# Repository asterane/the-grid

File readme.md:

# The Grid

# Table of Contents

1.  [Under Construction](#org4e31319)
2.  [Overview](#orgddce423)
3.  [Project Goals](#org27a8e06)
    1.  [Overall](#orgf33c17d)
    2.  [Design](#org3ddfc4e)
    3.  [Implementation](#orge4cc2e5)
4.  [System](#orgab08084)
    1.  [Origins](#org15afbf3)
    2.  [Considerations](#org984049b)
    3.  [Examination](#org4223284)
        1.  [Board](#org9094cac)
        2.  [Cube](#org7cbf77a)
        3.  [Column](#org4744b31)
        4.  [Grid](#orgfe13412)
        5.  [Control](#org2ae035e)
5.  [Structure](#org9b584a7)
6.  [Electronics](#orgca242fe)
7.  [Software](#org8aeed29)
8.  [Reflection](#org893cef3)

# Under Construction

This readme file will become much more extensive in the future.

# Overview

By far my most challenging and ambitious engineering project up to its
time, the Grid was a massive lighted display board which served as a
set piece for the play in my senior year of high school. The image
above shows the first time the entire Grid lit up at once. This
display wall was composed of 60 wooden cubes, each two feet by two
feet, for a total size of twenty feet at the base by twelve feet in
height. Every cube contained four high power red-green-blue (RGB)
light emitting diodes (LED) and acted as a single pixel.

A complex system, the Grid had many aspects, ranging from
architectural design to electronics manufacturing. I was the lead
engineer for the project; I designed every element of the Grid and its
production process, and oversaw the implementation. I owned this
project from conception to completion, keeping everything on schedule
and managing a team of other students throughout the process. As well
as engineering, I also managed the acquisition of all the components
we needed, making sure the director purchased them when necessary.

The various parts of the final product may be best understood by
working backwards from our desired results. This project's goal was to
construct an impressive lighted backdrop for a theatrical performance;
we chose sixty pixels as an artistically and logistically appropriate
resolution. Each pixel was a cube: a frame constructed of 2 by 4
lumber with a mounting panel midway in, behind a sheet of diffusing
plastic on the front. Four high power LEDs occupied each cube; all
four in any cube were always the same color.

Current had to be supplied to the LEDs, as they were simply packages
with solder pads. We constructed and connected current sources by
hand, one circuit board per cube, to drive the lights. Power for all
these custom LED drivers came from ten power supplies that we wired
with fuses ourselves, also by hand. Four Arduino microcontroller
boards switched on and off the current sources, and in turn the
LEDs. I wrote custom software to enable pulse width modulation on
every pin of these boards, allowing full dimming of each pixel.

All control signals were orchestrated by a Raspberry Pi computer that
acted as a server, accepting packets of lighting data from a client
computer and sending appropriate signals to the Arduinos to adjust the
pixels' light levels. The client computer was a laptop held by the
Grid operator, running custom software that provided a full graphical
interface to the Grid. This application could edit and save lists of
cues for shows; during each show, it sent thousands of frames to the
Grid server including animations and automatically generated
transitions.

We used the Grid during performances of *The Curious Incident of the
Dog in the Night-time*; it was the centerpiece of our technically
ambitious set. Work began three months prior to the show, which was a
short timeline for such a project considering that time in the
workshop was mostly limited to weekday after school
rehearsals. Nonetheless, we finished the Grid on time and as
specified; it was used for all four performances of the production. As
all things in theater, it was transient, being disassembled shortly
after the show.

Our show was commended by critics for the technical feat. There are
awards for high school theatrical productions in northern Virginia,
the "Cappies", and the Grid would have won in a technical category had
a pandemic not abruptly truncated the school year in March 2020. At my
school, technical theater was the extracurricular activity where real
engineering happened, and this was by far the largest project ever
attempted by our school's theater department. I hazard that it will
remain unmatched.

While I led the project, I also worked with a fantastic team of other
people, without whom this project would not have been possible. We
assembled something truly great together. One particular colleague of
mine contributed more than any other to the Grid. She personally wrote
thousands of lines of code to create the Grid client software, a
crucial part of the system that would not have otherwise come to
fruition. This is only the most notable of her efforts, and I give her
full credit for the client software.

This repository's top level directory is divided into a few
folders. The directories `structure`, `electronics`, and `software`
contain resources relevant to those aspects of the project,
respectively. The `media` directory holds a curated selection of
dozens of pictures and videos which exhibit the Grid in action. The
other files in this top directory are relevant to the entire
project. In the Bill of Materials is a listing of all the components
and tools used to assemble the lighting system. There is also a
diagram of the control architecture, and my first design document for
the Grid.

# Project Goals

## Overall

-   Build a huge, visually striking set piece with dynamic lighting
    elements to serve as the backdrop for a play
-   Display a sequence of designs during the show, including static
    images and animations
-   Surprise the audience with the breadth and scale of effects that may
    be shown on the display
-   Enhance immersion in the show by making the backdrop designs, and
    the piece itself, fit a certain aesthetic
-   Learn valuable techniques for multidisciplinary engineering and
    project management
-   Teach a team of other students how to effectively manufacture
    structures and electronics

## Design

-   Devise an inexpensive architecture, aiming to fit within a
    relatively low budget for such a project
-   Make the device look clean, modern, and monolithic from the
    audience's perspective
-   Primarily use available architectural materials, mostly wood, from
    the set workshop
-   Let the design be driven by requirements, and find the appropriate
    LED chips for the job
-   Come up with a switchable, cheap, easy to assemble current supply
    design using discrete components
-   Determine how to network many electronic parts together so that each
    receives necessary power
-   Use inexpensive computers to control the light array, writing all
    necessary algorithms by hand
-   Send images to the system remotely, from another computer, so that
    the operator may be elsewhere
-   Create cue software that enables graphical design of a sequential
    list of images for the display
-   Add an interface to the cue software to display images on the light
    array during the show

## Implementation

-   Manage and work with a team of people to assemble a massive object
    with many thousands of components
-   Find all necessary tools or parts and make sure that they are
    purchased when needed
-   Oversee inventory of components and equipment, looking out for
    losses or shortages
-   Instruct inexperienced students personally in disciplines like
    soldering and wiring
-   Work extensive quality control, fixing errors in construction that
    others failed to catch
-   Test all devices with care to ensure that nothing will break when
    the design scales up
-   Write hundreds of lines of code, fully test them, and optimize the
    software however needed
-   Lead the team, make sure there are tasks for people, and keep morale
    up throughout the project
-   Come up with fixes to unexpected issues right away, avoiding delays
    as much as possible
-   Do any critical job that abruptly comes up, spending as long as
    necessary to stay on track

# System

The above diagram depicts the Grid control system. I created it during
the software design process; it includes all the aspects of the final
system, as well as some features that we did not quite have time to
develop. Physical parts of the Grid are glossed over here, but are
certainly worth exploring as part of the overall system. In this
section, I will examine the Grid's components, the interactions
between them, and how they were all integrated into a functional,
controllable display. Much of the implementation detail will be saved
for the later sections specific to each system.

## Origins

I was given the original specification for this project near the end
of the school year before the show, my junior year. Our theater
director wanted what was essentially a grid of independently
controlled, colored lights for the next year's first show. The vision
for the design went through a few iterations before the summer
began. Regardless, it is far harder to bring such a device into being
than it is to talk about it. The director would agree that at the
time, he had no idea of the complexity of the system he was asking
for.

Shortly before the summer, we had a design meeting, during which I
brainstormed and wrote up my first design document for the Grid. My
first goal was to find an inexpensive and powerful LED component, as
this would drive the design of all of the other electronics. After
finding a three color, three watt LED chip, I set to work designing
the many systems that must interface together in a fully functional
digital display. I spent many summer mornings drawing design sketches
with pencil and paper; I find that this is always the best way to work
through complex problems.

## Considerations

Certain decisions about appearance and functionality must be made to
drive the rest of an engineered system's design. We knew that the Grid
should appear extremely large, make emotional impressions without
distracting the audience, and not be too complex to build in the time
we had. The maximum height for our stage is twelve feet, and we
calculated that twenty feet of width would make the Grid appear to
fill the stage while remaining visible to the entire audience.

Both dimensions are multiples of two, so we settled on pixels sized at
two feet by two feet. This size is easy to build and manageable to
work with; it required sixty cubes, two feet to an edge. Ten by six is
quite a low resolution, but this allowed us to minimize the amount of
electronics we had to build. It also fit the artistic goals of the
show, as a backdrop with high resolution images would have distracted
viewers from the actors' performances at the front of the stage.

I determined that diffusing the light from four RGB LEDs, dissipating
three watts of power each, would deliver an appropriate effect. It was
critical that every pixel be independently and instantly controllable,
at any time, in both color and brightness. This requirement drove the
design of the entire control system towards speed and
flexibility. With the above core points in mind, the interactions of
the many components of the Grid fell into place, as they all acted in
service to our central goals.

## Examination

This section will provide an overview of the entire Grid with an eye
to system integration. I will build my way up through ever larger and
more encompassing logical divisions of the Grid system, going over the
design and implementation that must come together for each one to take
its place and function as specified. The boards are the circuit
prototyping boards on which the LED drivers were assembled. The cubes
are the individual pixels that make up the display. Each column has
its power independently distributed. The Grid itself, of course, is
the entire display wall. The control system abstracts the Grid's
technical details and allows for relatively simple operation.

### Board

Once I knew the LED part I would be using, I needed to decide how best
to distribute power to 240 of them (60 cubes with 4 LEDs each). An
LED's brightness is a function of its current; small variations in
current often cause significant fluctuations in brightness. To avoid
such unsightly variance, I needed to ensure that constant current
would pass through each LED when it was turned on. This is in fact
more complicated than it appears at first, as every red-green-blue LED
package contains three independent diodes, one of each color.

Each individual diode is rated for about 350 milliamps of sustained
current. I wanted to get the most out of these LEDs, so that is the
current I targeted with my design. I sketched out possible schemes to
provide current to all three colors in a package with a single
circuit, which would have saved components. Unfortunately, it was not
to be; it would still have been possible for one diode to heat more
than the others, draw extra current, and go into thermal runaway,
probably burning out in the end.

In the end, the design needed 720 independent current sources (240 RGB
LEDs, 3 diodes each). Every current source needed to pull 0.35 amps
through its diode at all times when switched on. Some commercial
products get close to these requirements, but it turned out to be far
cheaper in this case to purchase individual components with which to
assemble current sources ourselves. My design required two resistors
and two transistors per current source to be soldered together in a
particular manner.

Since a cube contained 12 diodes (4 LED packages), it made sense to
construct circuit boards containing 12 current source LED drivers
each. We obtained perforated prototyping boards on which twelve
circuits and supporting connectors fit perfectly. I designed the
circuit and the board layout in Kicad, made several prototypes for
testing, and taught many other students to assemble boards by placing
components and then carefully soldering them in place. This will be
discussed more later, but we soldered over 15000 connections by hand.

Along with the drivers, each board included sixteen sockets to connect
the LEDs. With a common anode design, each LED package had a single
positive voltage input for all three diodes, and an independent
cathode for each one. Four sockets on the board provided voltage to
the LED packages, and the other twelve connected to the drivers, which
would be switched to choose whether current would be allowed to flow
through each diode. Three control inputs mediated this switching, one
for each color; they accepted 5 volt logic levels.

Power for all twelve diodes, which could reach a maximum of over
twelve watts (~4.2A at ~3V), was supplied through a pair of screw
terminals soldered to the circuit board and large enough to accept
thick power supply wires. Positive voltage was connected directly to
the LED anode sockets, and ground was connected to two ground rails
that ran down both sides of the board and connected to every current
source along the way. To complete the circuit and render the board
operational, LED packages had to be properly connected to the sockets.

-   Current Sources
    -   Knowing the kind of LED I would be using, I then needed to decide
        how to distribute power to all 240 of them
    -   An LED's brightness is a function of its current, and small
        variations in current can lead to significant fluctuations
    -   For this reason, I needed to ensure that constant current would
        pass thru each LED
    -   Every red green blue light emitting diode package in fact contains
        three independent LEDs, one of each color
    -   Every individual diode is rated for ~350 milliamps of current, so
        that is what I needed to provide
    -   I considered schemes to provide current to all three colors of a
        package with one circuit, but it would still have been possible
        for one chip to heat, draw more, and go into runaway
    -   In the end, it was necessary to include 720 independent current
        sources in the design, 0.35 A each
    -   It turned out to be far, far cheaper to purchase individual
        transistors and resistors with which to assemble current sources
        ourselves, as opposed to purchasing what was available
    -   Every cube (pixel) contained 12 current sources (4 LED
        packages \* 3 colors each); all were on the same circuit board
        and cooled with a PC case fan
    -   I designed the circuit and board layout in Kicad, did several
        prototyping passes, and taught others to build boards
    -   More discussion on this later, but our current sources, something
        like 15000 connections total, were all soldered by hand

### Cube

Home to four RGB LED packages and one driver circuit board, each cube
constituted a single pixel in the Grid's display. Like all of our
theatrical sets, the structure of the Grid was constructed from
lumber, wood sheets, and screws. These materials are readily available
in a technical theater workshop. It was easy to envision each of the
Grid's pixels as an independent piece of structure that could be built
on its own before being combined into the whole. Every cube was
composed of twelve lengths of two by four lumber, each about two feet
long, joined together with about thirty construction screws.

These wooden frames created a square border around each pixel of the
Grid, which contributed to its iconic look. We routed channels at
appropriate locations in the frame to permit a sheet of plywood to be
slid into place; this was a panel on which to mount the
electronics. The sides of the cubes got additional plywood panels,
which prevented light from bleeding within the structure, keeping each
pixel distinct from every other. Areas of each cube were strategically
painted black to prevent the final Grid from looking like it was made
out of wood.

-   remember the cooling fans
    -   cubes
        -   All of our theatrical sets are constructed primarily from
            lumber, wood sheets, and screws
        -   These are the materials we had available, so these are the
            materials from which the Grid's body was built
        -   It was easy to envision each pixel of the display as an
            independent structural component: a cube
        -   Every cube was made of 12 lengths of 2x4 lumber, each about 2
            feet long, joined with construction screws
        -   The frames led to an unavoidable square border around each
            pixel, which turned out to look quite cool
        -   Channels were routed at appropriate locations in the frame to
            allow a sheet of plywood to be slid into place as a panel to
            mount electronics on
        -   Additional panels were applied to the sides of the cubes to
            prevent light from bleeding between them within the structure
        -   After LEDs were installed on the front of said panel, a sheet of
            translucent, diffusing plastic was stretched over the front of
            the cube to spread the light out and form a large square pixel
        -   As part of the process, areas of each cube were strategically
            painted black, which prevented the final Grid from looking, from
            the front, like it was made of wood
    
    -   most of this should go under Grid
        -   Sixty cubes were manufactured in total; they were taken out to
            the stage and stacked in a rectangle, 10 by 6
        -   All cubes were carefully aligned to make the front surface would
            appear as flat and seamless as possible
        -   They were all screwed together in the back on all four sides,
            making the structure extremely solid
    
    -   Integration (almost all this goes here though)
        -   Having an electronic system design is one thing, but integrating
            it into a 12 foot high wooden structure is quite another
        -   As we finished building each cube, we affixed 4 LED packages to
            the mounting panel in its middle
        -   The LEDs went on the front of the panel, and all of the other
            electronics went on the back
        -   Before placing every LED, long connecting wires had to be
            soldered to its four pads and run through a hole to the back of
            the cube
        -   Thus, the Grid structure was built out of cubes onstage with all
            LEDs already installed
        -   After every circuit board was completed and tested, it had to be
            attached to the back of a cube's mounting panel
        -   Each circuit board had sixteen sockets for the sixteen wires
            from the LEDs, which had to be carefully connected with pliers
        -   In addition to those, there were three sockets for the control
            wires from the microcontrollers, which were much, much longer
            and had to be run across the back of the Grid and secured
        -   Sixty desktop computer case fans were acquired to cool the
            transistors of the circuit boards
        -   These, too, had to be mounted to the internal structure of the
            cube and connected to the circuit board for power
        -   The circuit boards could not be powered without the power
            supplies, which were placed in the third cube from the ground in
            each column
        -   Handmade power cables connected the supply output sockets to
            screw terminals on each circuit board
        -   More custom cables ran from the power supplies to backstage
            stage pin connectors

### Column

-   Supports
    -   The Grid may have been large and sturdy, but it was narrow
        compared to its width, making it prone to tipping
    -   Since dozens of people were going to be working and acting
        around the structure for weeks, it was necessary to fix this
    -   Simply widening the base of the Grid would suffice, for which
        purpose supports needed to be added
    -   I added diagonal supports to the front first; these needed to be
        short to evade notice by the audience
    -   The front supports only extended by about a foot, but this was
        enough to prevent tipping in that direction, especially because
        everyone stayed well away to avoid damaging the plastic sheets
    -   Rear supports were much more important, as techs would be
        working behind the structure for long periods
    -   I connected four long supports to the back of the grid, running
        from the floor to the third cube up from the bottom
    -   Skids connecting the ends of the supports to the base of the
        Grid proper kept everything firmly attached
    -   These large supports made the Grid practically unshakable, and
        as safe as any of our other sets
    -   I and several others even took to climbing on the back of the
        structure to access difficult areas

-   Power Supply
    -   Power into the auditorium stage is provided by 3 pin stage
        connectors, 120 volts at 60 hertz with a 20 amp maximum
    -   I needed to supply 720 independent current sources with 0.35
        amps direct current at around 3 volts
    -   The only way to do the step down safely was to use commodity
        power supplies
    -   The cheapest power supplies available supply 12 volts DC with a
        maximum of 30 amps of current
    -   These were the only commonly available supplies that satisfied
        my requirements without being too expensive; I acquired 10
    -   Each supply was to provide the power for one column of the Grid,
        or six circuit boards, or 72 current sources
    -   This is about 25 amps at 2.5 - 3.5 volts, but the supply voltage
        is mostly irrelevant because the current sources step it down
    -   That is not equivalent to 25 amps at 12 volts and so did not
        challenge the max power capability of the supplies; this
        prevented any voltage fluctuations or overheating
    -   A standard supply has a row of bare screw terminals, which are
        dangerous if uncovered, exposing people to line voltage
    -   These had to be dealt with, and we wanted switches and fuses on
        the power supplies, so covers were necessary
    -   I designed power supply covers in a CAD program, including holes
        for line power cable, output sockets, switch, fuses, voltmeter,
        and a cooling grille
    -   We had the covers and plastic feet to keep the supplies off wood
        3D printed, and assembled the final products

### Grid

-   Microcontrollers
    -   Each cube had three colors of LED: red, green, and blue, which
        had to be controlled independently
    -   With 60 cubes and 3 colors per cube, 180 control channels were
        needed to switch all of the LEDs
    -   I needed cheap programmable boards with many 5 volt logic
        outputs, so I went with the Arduino Mega
    -   Since each Arduino has 54 logic outputs, we needed four of them
        to cover the 180 channels that controlled the Grid
    -   Each circuit board had three control inputs that were connected
        to Arduino logic outputs
    -   A HIGH signal turned on the LED, while a LOW signal kept it off
    -   LEDs, of course, have no brightness controls, so it is necessary
        to mediate the brightness by switching rapidly
    -   By turning them on and off many times per second, but changing
        the amount of time they are on during each second, the LEDs can
        be made to appear to change in brightness
    -   The ATmega processors used in the Arduino have a small number of
        hardware PWM outputs, but I needed every output to be capable of
        pulse width modulation
    -   I ended up having to implement PWM dimming in software, writing
        a program in C++ that switched the logic outputs many times
        every second and dimmed the LEDs
    -   This nearly did not work because the processors run at only 4
        MHz, but the Arduinos were just fast enough
    -   By dimming the different colors different amounts, any color
        that is a combination of light colors may be achieved
    -   It is necessary, during the show, to constantly communicate to
        the Arduinos whether any colors need to be changed
    -   They can receive data over a serial connection; luckily, the
        computer we used to oversee them had four USB ports
    -   Each Arduino kept a list containing the brightness of every one
        of its channels
    -   They were sent little "packets" over serial connection
        consisting of a header for alignment, a channel number, and a
        light intensity, each a single byte
    -   On every PWM cycle, the boards checked for new packets and
        changed the brightness of relevant channels accordingly

### Control

-   Grid Server
    -   The four independent microcontrollers controlled the LEDs
        themselves, but they needed to be overseen
    -   For control of the entire Grid, a full fledged computer was
        necessary, so we got a Raspberry Pi 4
    -   This processor had a fast enough clock speed to communicate with
        an operator's client program and all four Arduinos at once
    -   It would be impractical for the Grid operator to be physically
        next to it at all times, so it was necessary to be able to send
        instructions about updating the display remotely
    -   This component is called the Grid server because it "serves"
        access to the Grid's physical display
    -   While the LEDs are connected to the Arduinos with hundreds of
        wires, the Arduinos connect to the server with only four USB
        cables
    -   The server itself, and by extension the entire Grid, is
        controlled over an Ethernet connection
    -   Our auditorium contains an isolated Ethernet network to control
        the many lighting fixtures, and it has ports in several
        convenient places, including backstage and the booth
    -   The server computer was connected to a backstage Ethernet port
        and assigned a static IP address
    -   The operator's computer, running the client program, was
        connected to an Ethernet port in the booth at the back of the
        auditorium, where the Grid is fully visible
    -   Listening on a TCP socket, the server made a connection with the
        client and prepared to receive control data
    -   Data came into the server in large chunks, with cube numbers
        associated with RGB color values
    -   The server mapped the cube numbers to the appropriate Arduinos
        and logic outputs thereof, and sent off serial packets
    -   Since packets were received over Ethernet and sent out over
        serial almost constantly, I placed these functions in separate
        threads so that they could run asynchronously
    -   This server computer was the point of access to the entire Grid,
        and I made an SSH connection into it and ran test and
        troubleshooting programs on many occasions

-   Grid Client
    -   I give full credit for this impressive piece of software to one
        of my friends, a technician and actor who wrote it in just a
        couple weeks and saved the Grid
    -   It was important to have a piece of software from which the Grid
        could be easily controlled
    -   Just sending data remotely, however, is not nearly enough, as
        entering data to be displayed as RGB images by hand would take a
        prohibitively long time
    -   Thus, we needed a program that provided a graphical interface to
        the Grid: a list of cues to be replayed during shows, all
        created using a software representation of the Grid on which
        colors could be changed with a few clicks
    -   We needed both a graphical user interface and extremely fast
        development time, so we chose to use Python and the Qt framework
    -   Python is not a great language for application development, but
        it is quick to write and fast enough for this one time purpose
    -   The Qt framework provides a system to build graphical interfaces
        relatively easily, and bindings to the GUI components for use
        within an event driven program
    -   My friend built an interface that featured a scrollable cue list
        with editable cue names and numbers
    -   Next to the list was a representation of the Grid: 60 boxes,
        colored according to the design stored in the selected cue
    -   It was also possible to choose transitions between different
        cues and set their length
    -   The most used transition in our show was a smooth fade from one
        design to another
    -   An editing mode was included in the software, allowing the
        operator to select any cube and set its color, then send the
        result to the Grid for viewing
    -   There was also a blind mode, enabling editing of cues without
        changing what appeared on the Grid
    -   One fantastic feature was the ability to create animations and
        store them in a cue, which allowed effects like rain or a game
        of Tetris to be created
    -   All of the cues were stored in a custom text file format, which
        was written by the software on every change and read on startup
    -   The software used a small routine which I wrote to send packets
        full of color data to the Grid server
    -   The software was optimized with threading so that transitions
        could be run, and packets sent, without causing the GUI to hang
        and become unresponsive
    -   I was the Grid operator during all four shows, and the Grid
        client performed admirably throughout

# Structure

// Finish

# Electronics

// Finish

# Software

// Finish

# Reflection

// Finish

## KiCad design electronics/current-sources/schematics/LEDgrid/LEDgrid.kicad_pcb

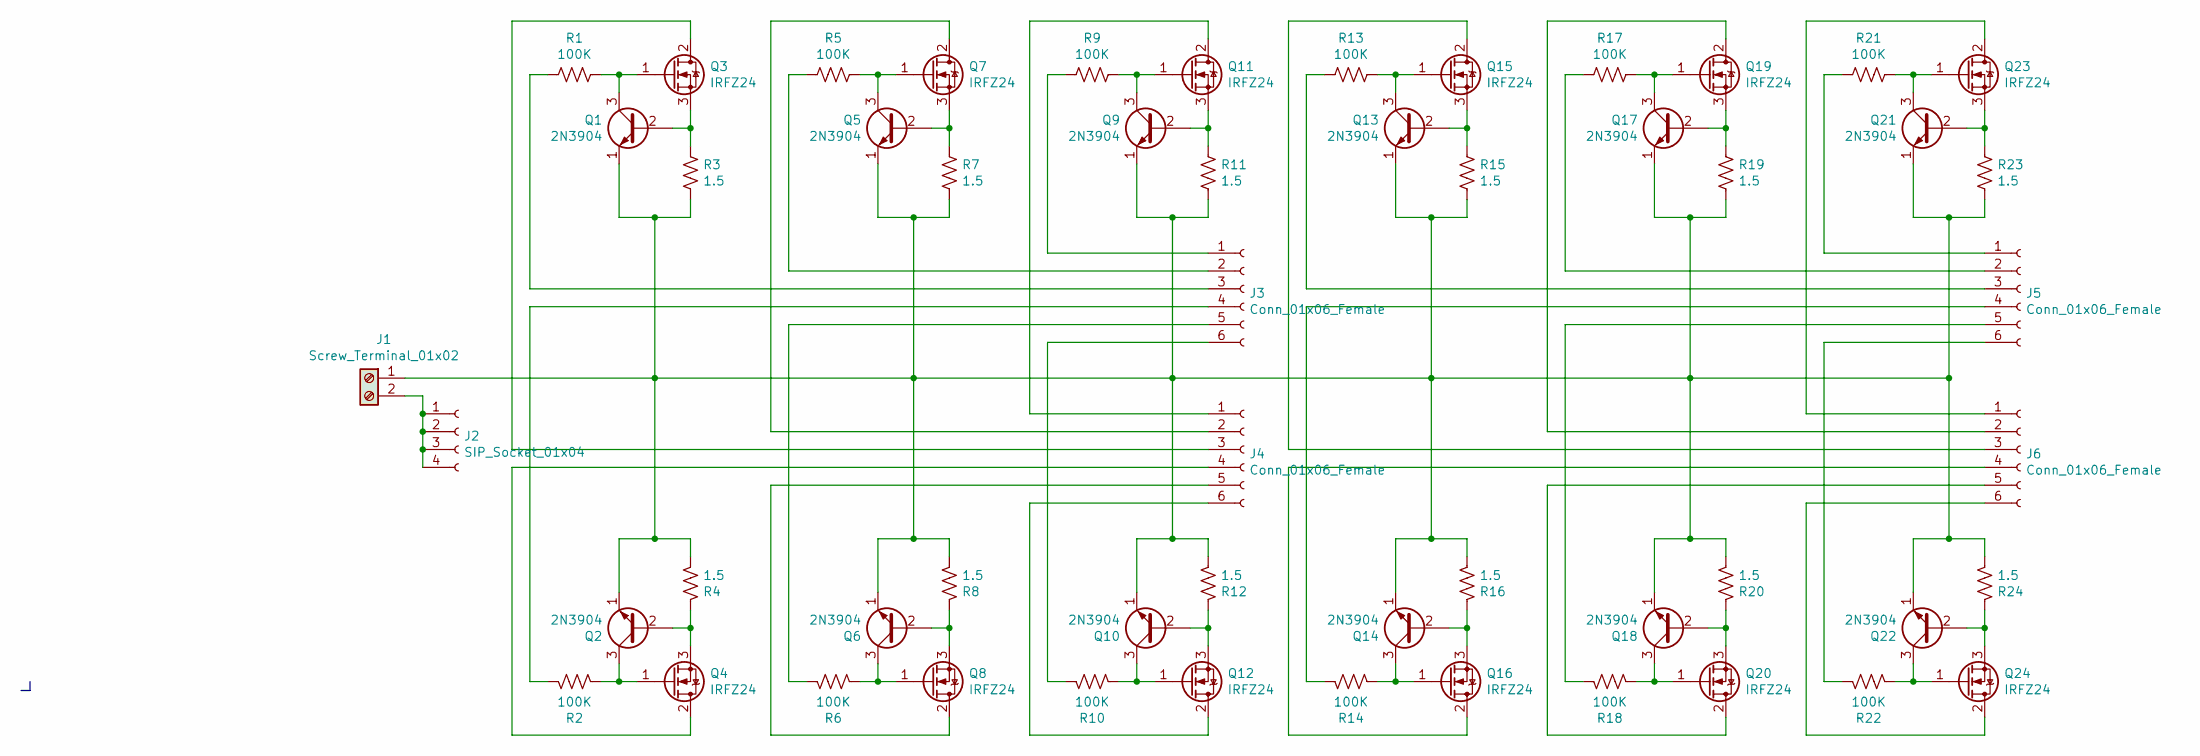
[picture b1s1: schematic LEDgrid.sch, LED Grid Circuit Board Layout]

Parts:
J1: Screw_Terminal_01x02; TerminalBlock_RND_205-00287_1x02_P5.08mm_Horizontal
J2: SIP_Socket_01x04; PinSocket_1x04_P2.54mm_Vertical
J3, J4, J5, J6: Conn_01x06_Female; PinSocket_1x06_P2.54mm_Vertical
Q1, Q2, Q5, Q6, Q9, Q10, Q13, Q14, Q17, Q18, Q21, Q22: 2N3904; TO-92_Inline_Wide
Q3, Q4, Q7, Q8, Q11, Q12, Q15, Q16, Q19, Q20, Q23, Q24: IRFZ24; TO-220-3_Vertical
R1, R2, R5, R6, R9, R10, R13, R14, R17, R18, R21, R22: 100K; R_Axial_DIN0207_L6.3mm_D2.5mm_P10.16mm_Horizontal
R3, R4, R7, R8, R11, R12, R15, R16, R19, R20, R23, R24: 1.5; R_Axial_DIN0207_L6.3mm_D2.5mm_P10.16mm_Horizontal

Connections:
unnamed: J1.1, Q1.1 (E), Q2.1 (E), Q5.1 (E), Q6.1 (E), Q9.1 (E), Q10.1 (E), Q13.1 (E), Q14.1 (E), Q17.1 (E), Q18.1 (E), Q21.1 (E), Q22.1 (E), R3.2, R4.2, R7.2, R8.2, R11.2, R12.2, R15.2, R16.2, R19.2, R20.2, R23.2, R24.2
unnamed: J1.2, J2.1, J2.2, J2.3, J2.4
unnamed: J3.1, R9.2
unnamed: J3.2, R5.2
unnamed: J3.3, R1.2
unnamed: J3.4, R2.2
unnamed: J3.5, R6.2
unnamed: J3.6, R10.2
unnamed: J4.1, Q11.2 (D)
unnamed: J4.2, Q7.2 (D)
unnamed: J4.3, Q3.2 (D)
unnamed: J4.4, Q4.2 (D)
unnamed: J4.5, Q8.2 (D)
unnamed: J4.6, Q12.2 (D)
unnamed: J5.1, R21.2
unnamed: J5.2, R17.2
unnamed: J5.3, R13.2
unnamed: J5.4, R14.2
unnamed: J5.5, R18.2
unnamed: J5.6, R22.2
unnamed: J6.1, Q23.2 (D)
unnamed: J6.2, Q19.2 (D)
unnamed: J6.3, Q15.2 (D)
unnamed: J6.4, Q16.2 (D)
unnamed: J6.5, Q20.2 (D)
unnamed: J6.6, Q24.2 (D)
unnamed: Q1.2 (B), Q3.3 (S), R3.1
unnamed: Q1.3 (C), Q3.1 (G), R1.1
unnamed: Q2.2 (B), Q4.3 (S), R4.1
unnamed: Q2.3 (C), Q4.1 (G), R2.1
unnamed: Q5.2 (B), Q7.3 (S), R7.1
unnamed: Q5.3 (C), Q7.1 (G), R5.1
unnamed: Q6.2 (B), Q8.3 (S), R8.1
unnamed: Q6.3 (C), Q8.1 (G), R6.1
unnamed: Q10.2 (B), Q12.3 (S), R12.1
unnamed: Q10.3 (C), Q12.1 (G), R10.1
unnamed: Q9.3 (C), Q11.1 (G), R9.1
unnamed: Q9.2 (B), Q11.3 (S), R11.1
unnamed: Q13.2 (B), Q15.3 (S), R15.1
unnamed: Q13.3 (C), Q15.1 (G), R13.1
unnamed: Q14.2 (B), Q16.3 (S), R16.1
unnamed: Q14.3 (C), Q16.1 (G), R14.1
unnamed: Q17.2 (B), Q19.3 (S), R19.1
unnamed: Q17.3 (C), Q19.1 (G), R17.1
unnamed: Q18.2 (B), Q20.3 (S), R20.1
unnamed: Q18.3 (C), Q20.1 (G), R18.1
unnamed: Q21.2 (B), Q23.3 (S), R23.1
unnamed: Q21.3 (C), Q23.1 (G), R21.1
unnamed: Q22.2 (B), Q24.3 (S), R24.1
unnamed: Q22.3 (C), Q24.1 (G), R22.1

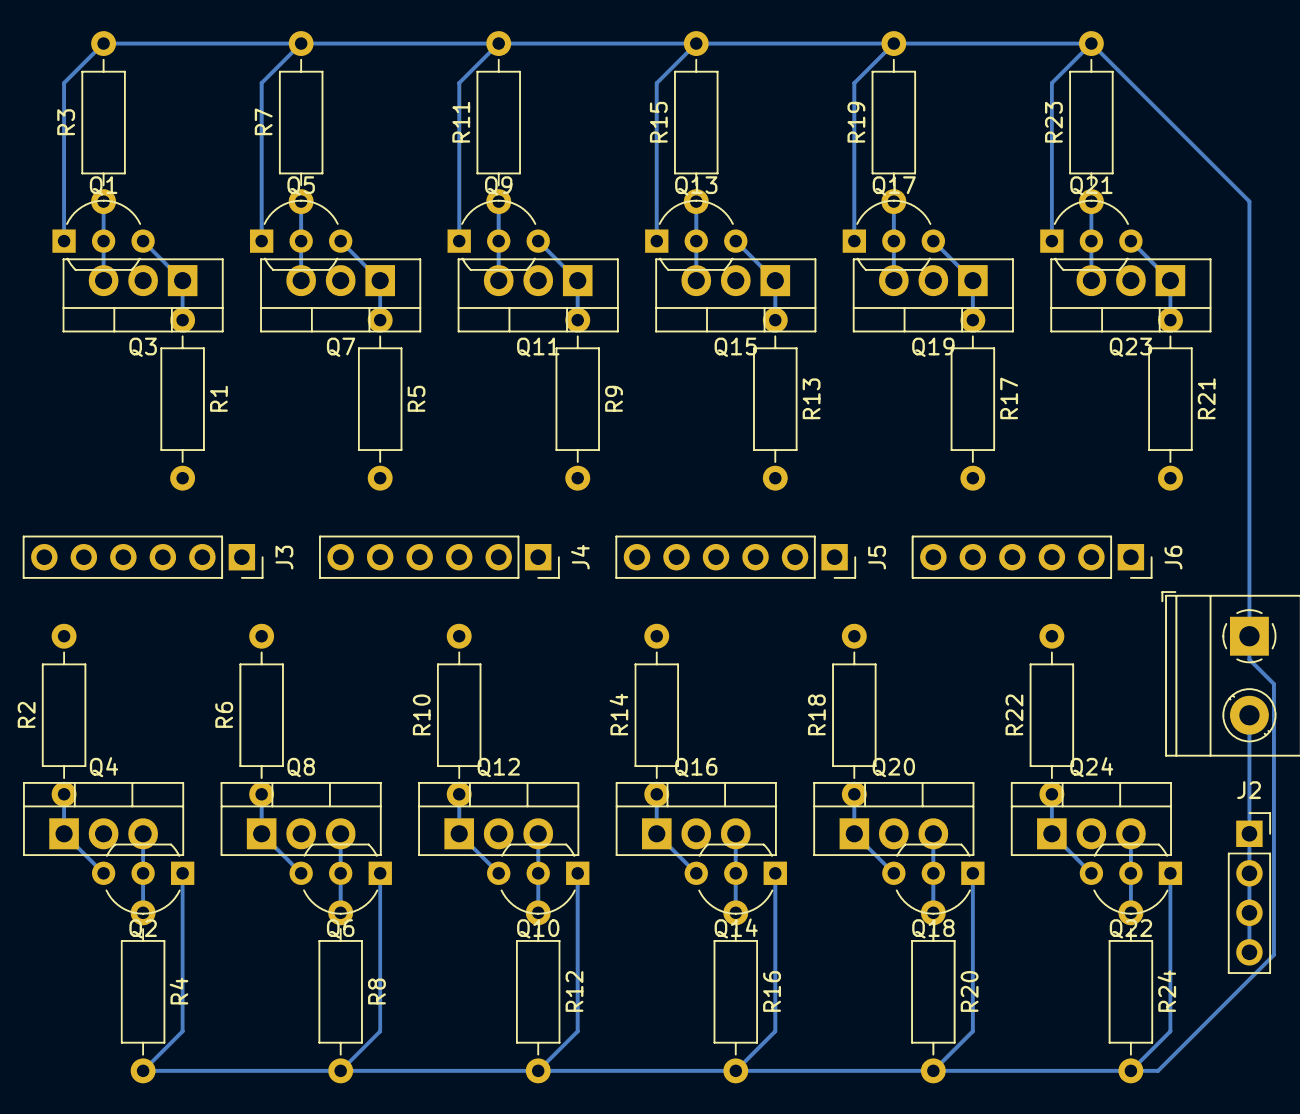
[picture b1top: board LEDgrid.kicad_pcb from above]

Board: 2 copper layers, 54 parts (0 on the bottom side), 50 nets.

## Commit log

2020-10-04 readme draft outline
2020-10-05 draft outline done
2020-10-06 overview finished
2021-12-15 adds additional circuit / board diagrams
2021-12-15 adds website skeleton
2021-12-21 moves website to main site repository
2022-03-30 adds SVG version of board layout diagram
